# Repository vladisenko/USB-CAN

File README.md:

# USB-CAN
Yet another USB-CAN adapter. Device based on STM32F072C8T6 mcu with USB and CAN peripherals. As the galvanic isolated CAN transceiver is used ISO1050 from TI. Boards communicate with PC by Virtual COM port with LAWICEL protocol.

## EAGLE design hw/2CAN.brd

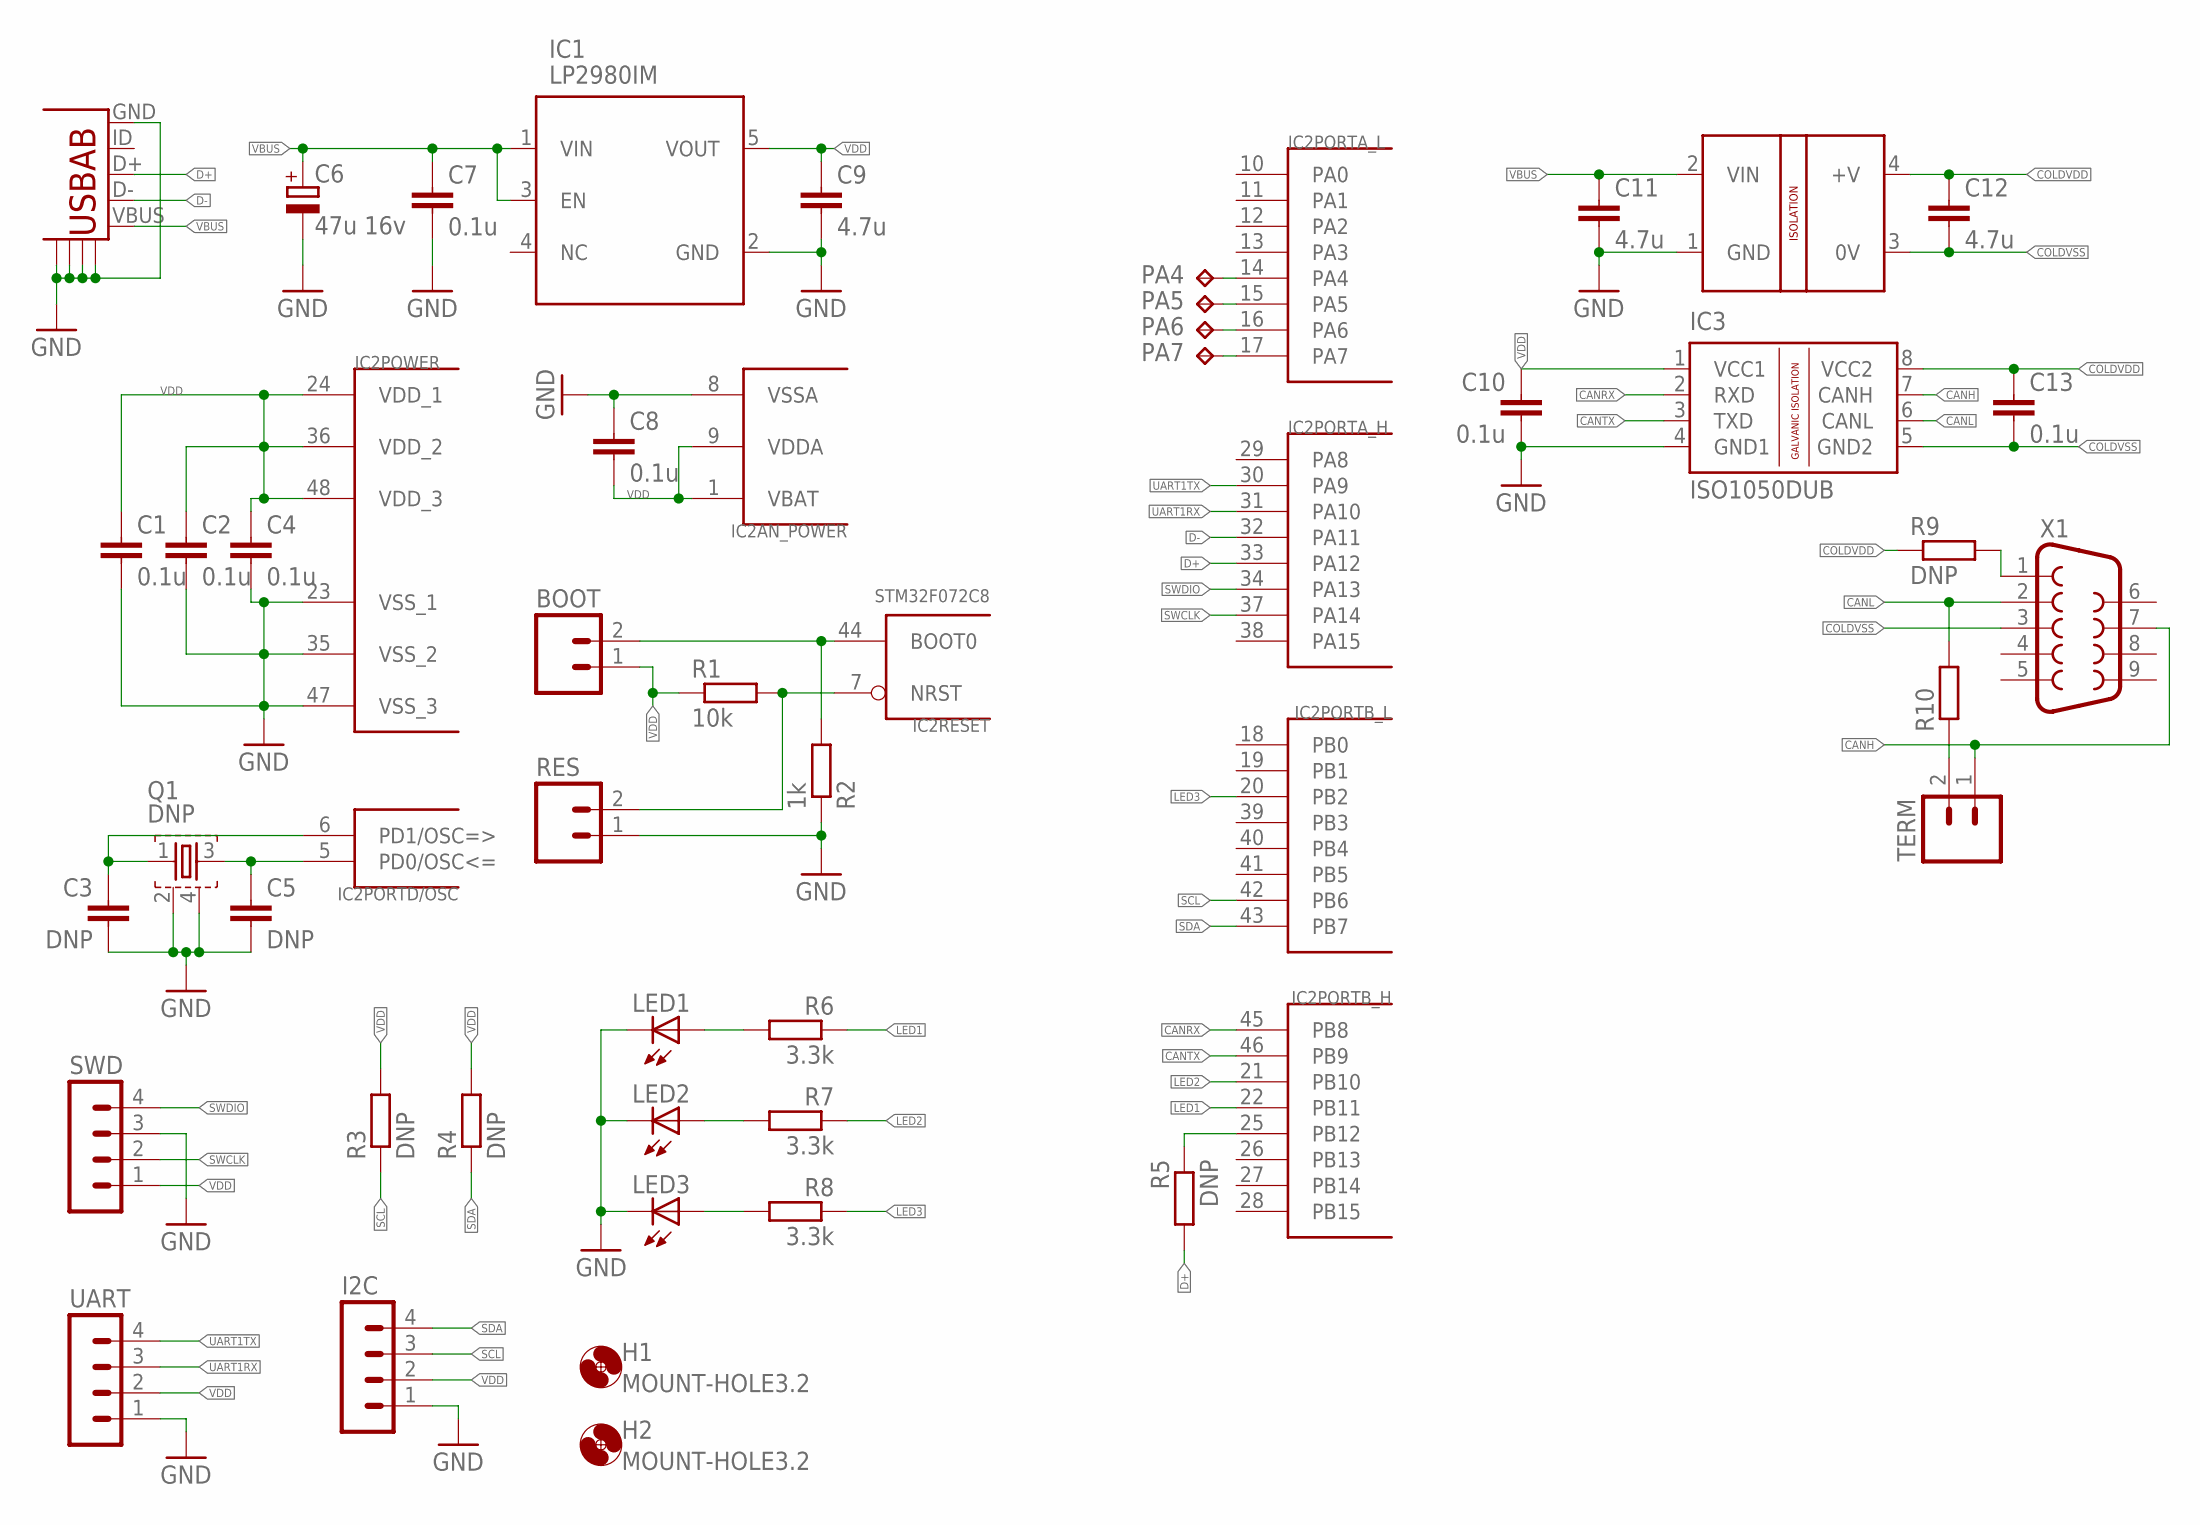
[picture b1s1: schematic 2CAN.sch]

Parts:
BOOT: M02PTH; 1X02
C1, C2, C4, C7, C8, C10, C13: 0.1u; C0603
C3, C5: DNP; C0603
C6: 47u 16v; E2-5
C9, C11, C12: 4.7u; C0805
H1, H2: MOUNT-HOLE3.2; 3,2
I2C: MA04-1
IC1: LP2980IM; SOT23-5L
IC2: STM32F072C8; TQFP48
IC3: ISO1050DUB; DUB-R-PDSO-G8
LED1, LED2, LED3: LEDSML0603; SML0603
PA4, PA5, PA6, PA7: TPB1,27; B1,27
Q1: DNP; FA-20H
R1: 10k; R0603
R2: 1k; R0603
R3, R4, R5: DNP; R0603
R6, R7, R8: 3.3k; R0603
R9: DNP; R0805
R10: R-EU_R0805; R0805
RES: M02PTH; 1X02
SWD: MA04-1
TERM: M02PTH; 1X02
U$1: USB_AB; USB-AB-MICRO-SMD
U$2: B0505SV; B0505S_V
UART: MA04-1
X1: DB9MALE; DB9_MALE

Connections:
CANH: IC3.7 (CANH), TERM.1, X1.7
CANL: IC3.6 (CANL), R10.2, X1.2
CANRX: IC2.45 (PB8), IC3.2 (RXD)
CANTX: IC2.46 (PB9), IC3.3 (TXD)
COLDVDD: C12.1, C13.1, IC3.8 (VCC2), R9.1, U$2.4 (+V)
COLDVSS: C12.2, C13.2, IC3.5 (GND2), U$2.3 (0V), X1.3
D+: IC2.33 (PA12), R5.2, U$1.D+
D-: IC2.32 (PA11), U$1.D-
GND: C1.2, C2.2, C3.2, C4.2, C5.2, C6.-, C7.2, C8.1, C9.2, C10.2, C11.2, I2C.1, IC1.2 (GND), IC2.8 (VSSA), IC2.23 (VSS_1), IC2.35 (VSS_2), IC2.47 (VSS_3), IC3.4 (GND1), LED1.C, LED2.C, LED3.C, Q1.2, Q1.4, R2.1, RES.1, SWD.3, U$1.GND, U$1.GND@1, U$1.GND@2, U$1.GND@3, U$1.GND@4, U$2.1 (GND), UART.1
LED1: IC2.22 (PB11), R6.1
LED2: IC2.21 (PB10), R7.1
LED3: IC2.20 (PB2), R8.1
unnamed: IC2.7 (NRST), R1.2, RES.2
unnamed: BOOT.2, IC2.44 (BOOT0), R2.2
unnamed: R9.2, X1.1
unnamed: LED1.A, R6.2
unnamed: LED2.A, R7.2
unnamed: LED3.A, R8.2
unnamed: R10.1, TERM.2
unnamed: C5.1, IC2.5 (PD0/OSC<=), Q1.3
unnamed: C3.1, IC2.6 (PD1/OSC=>), Q1.1
unnamed: IC2.14 (PA4), PA4.TP
unnamed: IC2.15 (PA5), PA5.TP
unnamed: IC2.16 (PA6), PA6.TP
unnamed: IC2.17 (PA7), PA7.TP
SCL: I2C.3, IC2.42 (PB6), R3.1
SDA: I2C.4, IC2.43 (PB7), R4.1
SWCLK: IC2.37 (PA14), SWD.2
SWDIO: IC2.34 (PA13), SWD.4
UART1RX: IC2.31 (PA10), UART.3
UART1TX: IC2.30 (PA9), UART.4
USBPU: IC2.25 (PB12), R5.1
VBUS: C6.+, C7.1, C11.1, IC1.1 (VIN), IC1.3 (EN), U$1.VBUS, U$2.2 (VIN)
VDD: BOOT.1, C1.1, C2.1, C4.1, C8.2, C9.1, C10.1, I2C.2, IC1.5 (VOUT), IC2.1 (VBAT), IC2.9 (VDDA), IC2.24 (VDD_1), IC2.36 (VDD_2), IC2.48 (VDD_3), IC3.1 (VCC1), R1.1, R3.2, R4.2, SWD.1, UART.2

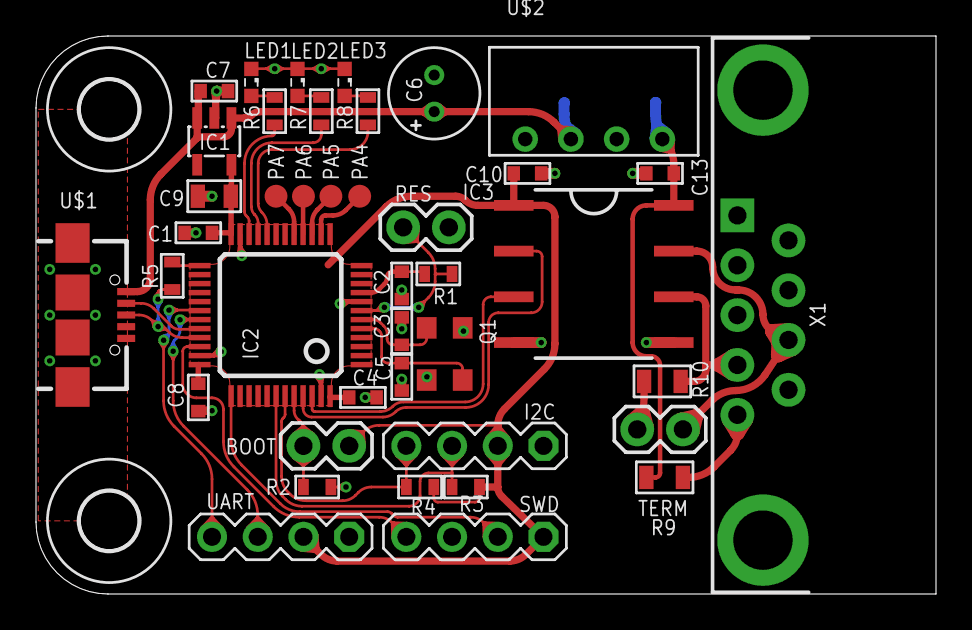
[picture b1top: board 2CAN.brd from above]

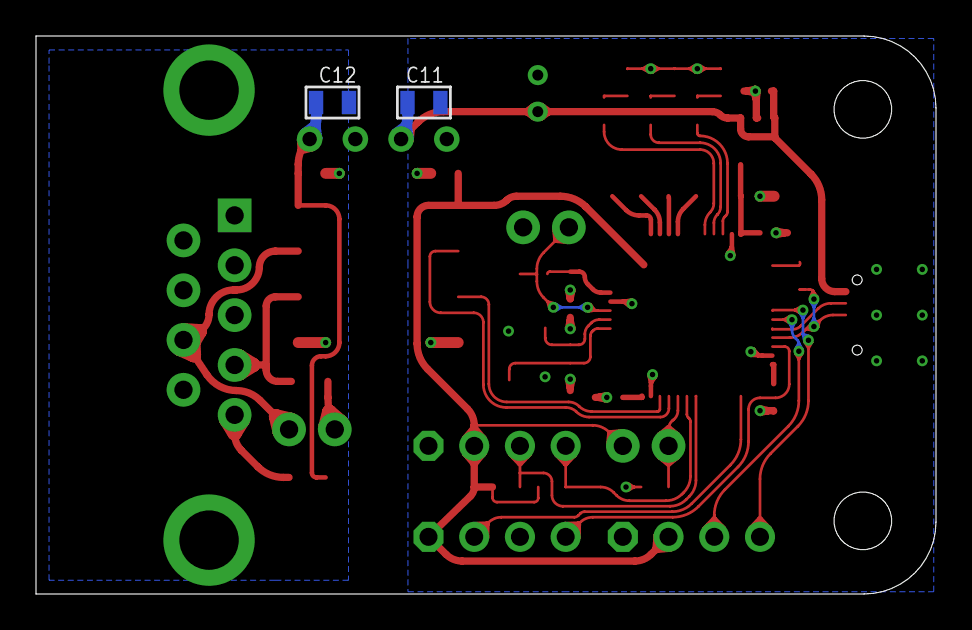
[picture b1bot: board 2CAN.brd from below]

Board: 2 copper layers, 50.0 x 31.0 mm, 45 parts (2 on the bottom side), 34 nets.

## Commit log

2017-03-29 :circus_tent: Added .gitattributes & .gitignore files
2017-03-29 edit .gitignore
2017-03-29 edit main
2017-03-30 add custom baudrate
2017-03-30 add hardware
2017-04-09 add pics
2018-06-04 fix performance
2018-10-15 add bitrate calculator
2018-12-26 update gitignore
2019-03-05 fix transmitting of IDE frames
2019-03-07 fix led issue
2019-08-06 fix issue with sending zero length data frame
2022-01-08 add error reporting
2022-01-09 add draft for EEPROM
